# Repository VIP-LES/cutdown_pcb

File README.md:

# Cutdown PCB – MK5

## Overview

This repository contains the **MK5** revision of the custom PCB used in the Spring 2025 high-altitude balloon cutdown payload. The board integrates all key circuitry for telemetry, sensor data acquisition, LoRa radio communication, and the nichrome-based cutdown system.

Designed and iterated over **11 fabrication runs** (I know, it was painful), this board represents the final, flyable hardware developed using Georgia Tech’s **HIVE** LKPF Protomat and Protolaser systems.

## Fabrication Notes

- **Board Fabrication**: All prototypes were milled and laser-etched in-house using the HIVE’s LPKF Protomat and Protolaser equipment.
- **Inspection**: Due to tooling artifacts, each board required **intense microscope inspection** to manually remove stray micron-level copper bridges using an X-Acto knife and fine probes.
- **Reliability**: The final revision performed successfully in flight, powering the payload and handling cutdown operations as designed.

## Additional Info

The board connects directly to an Adafruit Feather M0 RFM9x and routes power, sensors (MS8607), and nichrome cutdown lines through onboard circuitry. It is designed for compact, modular integration into the balloon payload stack.

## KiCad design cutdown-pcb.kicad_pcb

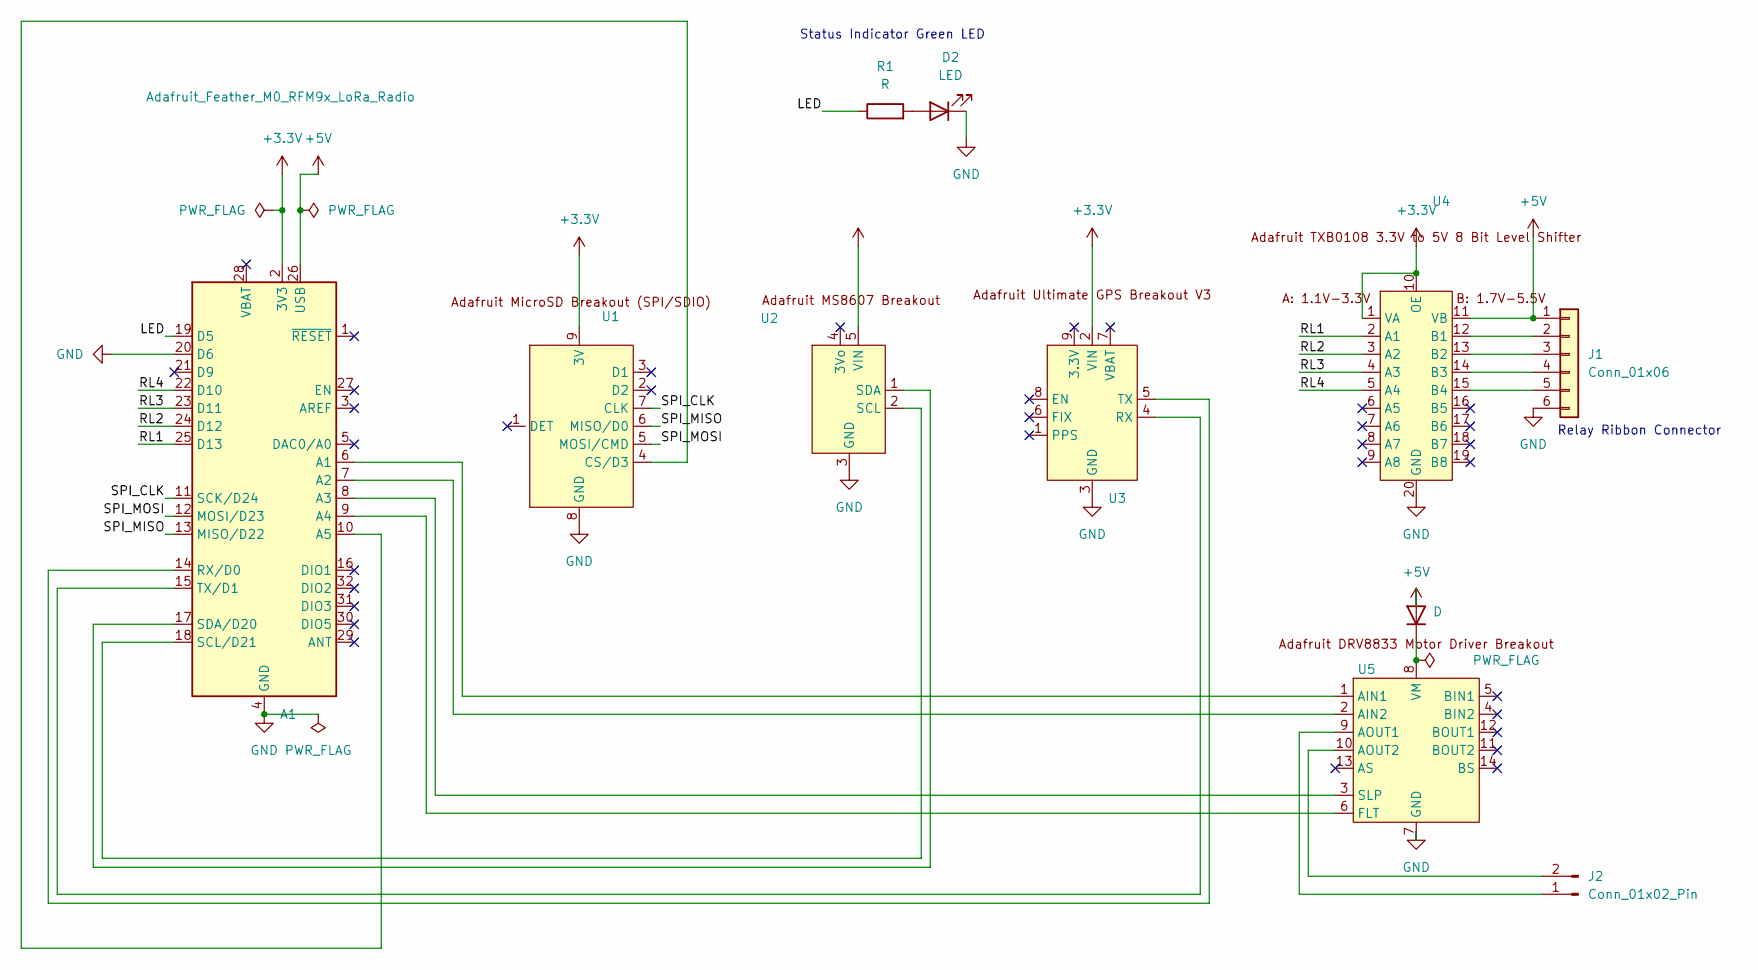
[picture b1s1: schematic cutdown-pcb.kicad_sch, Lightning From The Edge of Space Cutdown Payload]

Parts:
A1: Adafruit_Feather_M0_RFM9x_LoRa_Radio; Adafruit_Feather_M0_RFM
D1: D; D_DO-35_SOD27_P10.16mm_Horizontal
D2: LED; LED_D5.0mm
J1: Conn_01x06; PinHeader_1x06_P2.54mm_Vertical
J2: Conn_01x02_Pin; PinHeader_1x02_P2.54mm_Vertical
R1: R; R_Axial_DIN0207_L6.3mm_D2.5mm_P10.16mm_Horizontal
U1, U3: PinSocket_1x09_P2.54mm_Vertical
U2: PinSocket_1x05_P2.54mm_Vertical
U4: Adafruit8BitLevelShifter
U5: AdafruitMotorDriverBreakout

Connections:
+3.3V: A1.2 (3V3), U1.9 (3V), U2.5 (VIN), U3.2 (VIN), U4.1 (VA), U4.10 (OE)
+5V: A1.26 (USB), D1.2 (A), J1.1, U4.11 (VB)
/LED: A1.19 (D5), R1.1
/RL1: A1.25 (D13), U4.2 (A1)
/RL2: A1.24 (D12), U4.3 (A2)
/RL3: A1.23 (D11), U4.4 (A3)
/RL4: A1.22 (D10), U4.5 (A4)
/SPI_CLK: A1.11 (SCK/D24), U1.7 (CLK)
/SPI_MISO: A1.13 (MISO/D22), U1.6 (MISO/D0)
/SPI_MOSI: A1.12 (MOSI/D23), U1.5 (MOSI/CMD)
GND: A1.4 (GND), A1.20 (D6), D2.1 (K), J1.6, U1.8 (GND), U2.3 (GND), U3.3 (GND), U4.20 (GND), U5.7 (GND)
unnamed: A1.6 (A1), U5.1 (AIN1)
unnamed: A1.7 (A2), U5.2 (AIN2)
unnamed: A1.8 (A3), U5.3 (SLP)
unnamed: A1.9 (A4), U5.6 (FLT)
unnamed: A1.10 (A5), U1.4 (CS/D3)
unnamed: A1.14 (RX/D0), U3.5 (TX)
unnamed: A1.18 (SCL/D21), U2.2 (SCL)
unnamed: A1.17 (SDA/D20), U2.1 (SDA)
unnamed: A1.15 (TX/D1), U3.4 (RX)
unnamed: D1.1 (K), U5.8 (VM)
unnamed: D2.2 (A), R1.2
unnamed: J1.2, U4.12 (B1)
unnamed: J1.3, U4.13 (B2)
unnamed: J1.4, U4.14 (B3)
unnamed: J1.5, U4.15 (B4)
unnamed: J2.1, U5.9 (AOUT1)
unnamed: J2.2, U5.10 (AOUT2)

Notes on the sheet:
Status Indicator Green LED
Relay Ribbon Connector

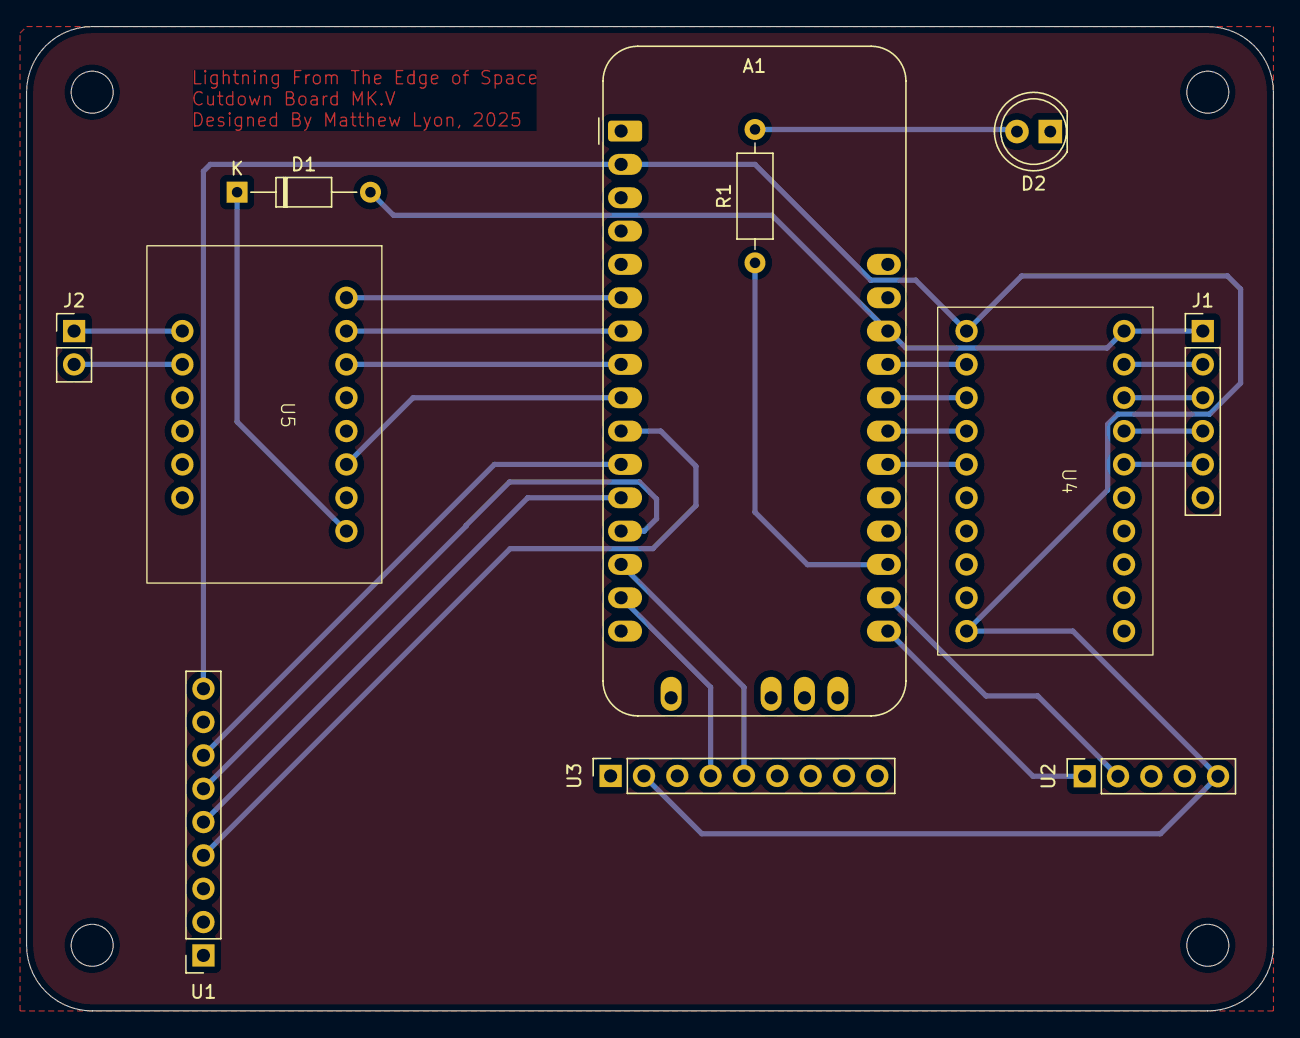
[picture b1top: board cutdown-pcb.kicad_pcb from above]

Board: 2 copper layers, 95.0 x 75.0 mm, 11 parts (0 on the bottom side), 28 nets.

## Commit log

2025-04-02 Intial PCB build 1
2025-04-03 Version 3
2025-04-18 Final SP '25 Flyable PCB and Cutdown board laser files
